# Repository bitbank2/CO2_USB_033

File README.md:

CO2_USB_033
===========
<b>What is it?</b><br>
A KiCad PCB project plus firmware for a portable CO2 sensor based on the WCH CH32X033 MCU. This is my first PCB with this chip and so far it's impressing me quite a bit. I was able to buy a small quantity for about 23 cents each. The 033 is part of the CH32X035 family and has a 48Mhz RISC-V core with 20K SRAM, 62K FLASH, USB full speed and many of the typical I/O capabilities of 32-bit MCUs. This project was more of an experiment to see if I could easily add some USB functionality to my battery powered CO2 sensor.<br><br>
<b>What's special about this project?</b><br>
By using a low cost display, MCU and sensor, my aim for this project was to make a practical and low cost way to carry a true CO2 sensor in your pocket. The CH32X033 also allowed me to easily add USB CDC support so that a PC could receive the sensor readings too. I use a clever single pushbutton circuit to control power and input. By using the enable pin of the 3.3v regulator in software control, the device can turn itself off. I use this feature to make sure the battery isn't accidentally left for dead. After 5 minutes of use, it will turn itself off.<br><br>
<b>Building the Project</b><br>
I used KiCad to design the PCB and all of the source files and Gerber zip is in the PCB folder ready to send for production. I assembled the board myself, so I don't have any assembly instructions/files with it. The firmware was built using MounRiver Studio IDE and the CH32X035 EVT provided on the WCH website.<br>

If you find this code useful, please consider sending a donation or becoming a Github sponsor.

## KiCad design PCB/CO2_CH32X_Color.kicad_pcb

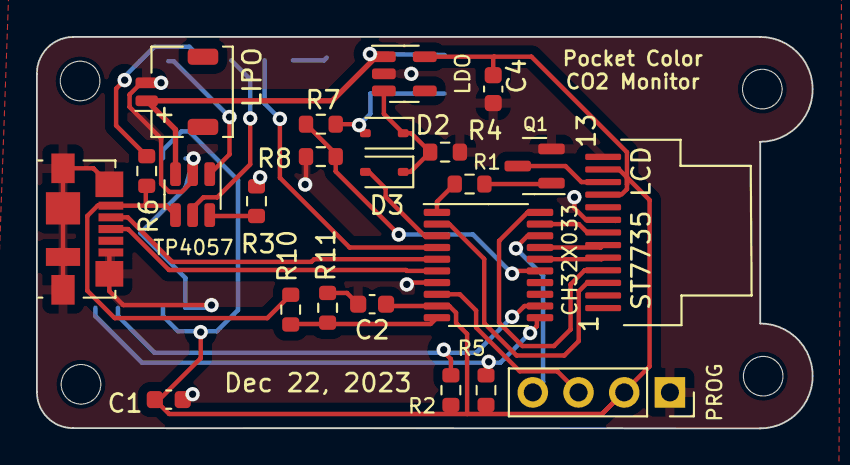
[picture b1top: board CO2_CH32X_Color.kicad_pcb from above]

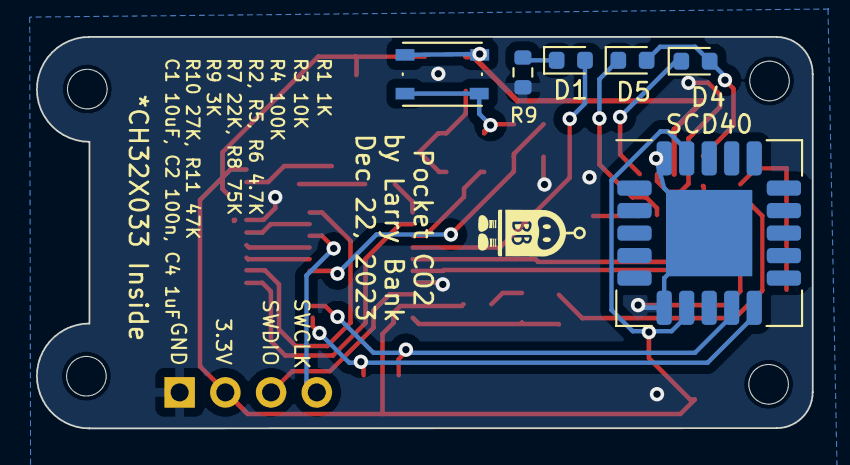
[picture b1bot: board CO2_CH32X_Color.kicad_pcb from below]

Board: 2 copper layers, 43.1 x 21.8 mm, 33 parts (6 on the bottom side), 29 nets.

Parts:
C1: 10uF; C_0603_1608Metric
C2: 100n; C_0603_1608Metric
C4: 1uF; C_0603_1608Metric
CH32X033: TSSOP-20_4.4x6.5mm_P0.65mm
D1, D4, D5: LED; LED_0603_1608Metric
D2, D3: D; D_SOD-323
H1, H2, H3, H4: MountingHole; MountingHole_2.2mm_M2_DIN965
LDO: AP2127K-3.3; SOT-23-5
LIPO: Battery_Cell; JST_SHL_SM02B-SHLS-TF_1x02-1MP_P1.00mm_Horizontal
PROG: Conn_01x04_Socket; PinSocket_1x04_P2.54mm_Vertical
PUSH0: SW_Push; SW_Push_1P1T_NO_Vertical_Wuerth_434133025816
Q1: AO3400A; SOT-23
R1: 1k; R_0603_1608Metric
R2, R5, R6: 4.7K; R_0603_1608Metric
R3: 10K; R_0603_1608Metric
R4: 100K; R_0603_1608Metric
R7: 22K; R_0603_1608Metric
R8: 75K; R_0603_1608Metric
R9: 3K; R_0603_1608Metric
R10: 27K; R_0603_1608Metric
R11: 47K; R_0603_1608Metric
SCD40: SCD41-D-R2; Sensirion_SCD4x-1EP_10.1x10.1mm_P1.25mm_EP4.8x4.8mm
TP4057: TP4057; SOT-23-6
U4: ST7735_13pin
USB1: USB_B_Micro; USB_Micro-B_Molex_47346-0001

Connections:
+3.3V: C1.1, C2.1, C4.1, CH32X033.9 (VDD), LDO.5 (VOUT), PROG.2, R2.1, R5.1, SCD40.7 (VDD), SCD40.19 (VDDH), U4.10 (VDD), U4.12 (LED_A)
BATT_DIV: CH32X033.15 (PA1), R7.1, R8.2
CS: CH32X033.19 (PA4/CS), U4.7 (CS)
DM: CH32X033.5 (PC16/UDM), USB1.2 (D-)
DP: CH32X033.6 (PC17/UDP), USB1.3 (D+)
D/C: CH32X033.16 (PA2), U4.5 (D/C)
GND: C1.2, C2.2, C4.2, CH32X033.7 (GND), LDO.2 (GND), LIPO.2 (-), PROG.1, Q1.2 (S), R3.2, R4.1, R8.1, R9.1, R11.1, SCD40.6 (GND), SCD40.20 (GND), SCD40.21 (GND), TP4057.2 (GND), U4.8 (GND), U4.13 (GND), USB1.5 (GND), USB1.6 (Shield)
LCD_BL: CH32X033.1 (PA6/MISO), R1.1
LED1: CH32X033.4 (PB7), D1.2 (A)
LED_K: Q1.3 (D), U4.11 (LED_K)
MOSI: CH32X033.2 (PA7/MOSI), U4.3 (DIN)
unnamed: D1.1 (K), R9.2
unnamed: D2.1 (K), D3.1 (K), LDO.3 (EN), R4.2
unnamed: D4.2 (A), D5.2 (A), R6.1
unnamed: D4.1 (K), TP4057.1 (CHRG)
unnamed: D5.1 (K), TP4057.5 (STDBY)
unnamed: Q1.1 (G), R1.2
unnamed: R3.1, TP4057.6 (PROG)
POWER_PIN: CH32X033.3 (PB1), D3.2 (A)
RESET: CH32X033.17 (PA3), U4.6 (RESET)
SCK: CH32X033.20 (PA5/SCK), U4.4 (CLK)
SCL: CH32X033.12 (PA10/SCL), R2.2, SCD40.9 (SCL)
SDA: CH32X033.11 (PA11/SDA), R5.2, SCD40.10 (SDA)
SWCLK: CH32X033.18 (PC19/SWCLK), PROG.4
SWDIO: CH32X033.8 (PC18/SWDIO), PROG.3
VBAT: LDO.1 (VIN), LIPO.1 (+), PUSH0.1, TP4057.3 (BAT)
VBUS: R6.2, R10.2, TP4057.4 (VIN), USB1.1 (VBUS)
VBUS_SENSE: CH32X033.10 (PA9/MISO), R10.1, R11.2
VIN: D2.2 (A), PUSH0.2, R7.2

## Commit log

2024-01-07 First version working with sensor values going to CDC serial
2024-01-08 Added KiCad files
2024-01-08 added photo
